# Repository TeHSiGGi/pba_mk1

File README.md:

# PBA MK1

## Introduction

The **P**ortable **B**luetooth **A**mp MK1 is the first iteration of a portable bluetooth amplifier.

The goal was to design a universal base platform for designing bluetooth speaker in a range of small to large power.

The amplifier is meant to be powered by LiPo batteries.

## Repository structure

```text
/pba:mk1
  /docs             # Documentation repository
  /eagle            # Contains eagle files
  /gerber           # Contains gerber board files
  /pdf              # Contains PDF versions of the schematics 
```

## Technical specification

### Power Supply

The power supply provides different voltages for digital and analog purpose.

It provides the following rails:

- `D33` - 3.3V 0.25A Digital - for digital logic and bluetooth module
- `A75` - 7.5V 0.10A Analog - for analog audio processing
- `D120` - 12V 1.00A Digital - Control voltage for Class-D amplifier
- `VAMP` - VBAT - 30V 3.00A - Amplification voltage for Class-D amplifier

The `D33` rail is constantly enabled and provides power for the bluetooth module.

All other rails are enabled on demand by the bluetooth module, via the `EN` signal.

As regulators for all rails expect `VAMP` `LMR50410` are used.

The `VAMP` rail can be varied between `VBAT` and 30V. This is provided by using a `LM5122` boost converter, that will be enabled on demand. If not required, the `LM5122` will go into passthrough mode and disable the boost action. The boost action is controlled via a separate `LVL` signal.

The power supply also provides the capability to charge and use a 4S LiPo battery. Please note: The power supply does **not** provide any balancing or protection circuitry. Those things must be included in your 4S LiPo battery pack.

As charging controller a `LTC4006-6` is used, which incorporates all necessary functionality.
The power supply used to charge the LiPo battery is a 19V external power supply. The input current is limited to 3.07A.

Charging current is limited to 2.00A and the charging timer is configured to approx. 2 hours.

There is currently **no** NTC readout configured in the charging circuit.

As a charger supply, I recommend the use of generic laptop chargers with 19V and 3.54A - they are widely available, reliable and cheap.

### Amplifier and DAC

As amplifiers there are two `TPA3245` used in this project.

The first of them is driven by directly by the `CSR8675` bluetooth chip DAC outputs, using a BTL configuration for two output channels.

The second amplifier is configured in a PBTL configuration and is driven by a `PCM5102` DAC.

The first amplifier should be used for full-range or dedicated mid/migh-range speakers, whereas the second amplifier with its PBTL configuration is meant to drive low-range/subwoofer speakers, since due to its configuration it is able to deliver more current and drive speakers with low impedances.

All analog signals are used differentially to reduce noise and hum. Between the differential DAC output and amplifier inputs there are `TS914` adding amplification to the signals for additional volume.

The amplifiers will automatically be enabled, if music is playing. This is controlled by the `CSR8675` using the `AMP_EN` signal.

There is an additional level detection circuit that will switch the amplifier supply voltage by setting the `LVL` signal to `high`. This allows the amplifier chips to run at a lower voltage for moderate volumes and have enough headroom for high volume music playback. The usage of a higher voltage also allows for better use of higher impedance speakers, such as 8-16Ohms.

The threshold of the level detection can be configured via a potentiometer on the amplifier board.

### Bluetooth

As for bluetooth, the `CSR8675` in form of `BTM-875` modules is used.

That chip provides the following functionality:

- Bluetooth 4.0+ compliance
- Stereo differential analogue audio inputs (used as line-in)
- Stereo differential analogue audio outputs (driving `TPA3245` in BTL configuration)
- I²S output (driving `PCM5102` for second `TPA3245` in PBTL configuration)
- LED and Button GPIOs (3 LEDs and 8 GPIOs are exposed)
- GPIO control for enabling external circuitry (enabling power with `EN` and amplifiers with `AMP_EN`)
- Kalimba DSP (used for crossover and DSP audio processing)
- True Wireless Stereo (can link two amplifiers together playing music in sync)

Software used on the `CSR8675` is configured using the ADK in version 4.1.35.

### Architecture

#### Audio signal paths

#### Power paths

#### GPIO to function mapping

|GPIO|Function|Description|
|--|--|--|
|LED0|User interface LED|Can be used to display status messages.|
|LED1|User interface LED|Can be used to display status messages.|
|LED2|User interface LED|Can be used to display status messages.|
|PIO0|User interface GPIO|Can be used to connect a button for user interaction.|
|PIO1|User interface GPIO|Can be used to connect a button for user interaction.|
|PIO2|User interface GPIO|Can be used to connect a button for user interaction.|
|PIO3|User interface GPIO|Can be used to connect a button for user interaction.|
|PIO4|User interface GPIO|Can be used to connect a button for user interaction.|
|PIO5|User interface GPIO|Can be used to connect a button for user interaction.|
|PIO6|User interface GPIO|Can be used to connect a button for user interaction.|
|PIO7|User interface GPIO|Can be used to connect a button for user interaction.|
|PWR|User interface GPIO|Can be used to connect a button for user interaction.|
|PIO10|DETECT|Used to detect plugged in line-in source.|
|PIO11|AMP_EN|Used to enable amplifiers when music is playing.|
|PIO12|EN|Used to enable the power supply.|
|PIO15|I²S DAC enable|Used to enable the external I²S dac if music is playing.|

### Miscellaneous

Schematics and layouts are created using Eagle.

Gerber files provided have been used to create first batch of boards and working instances of the PBA MK1.

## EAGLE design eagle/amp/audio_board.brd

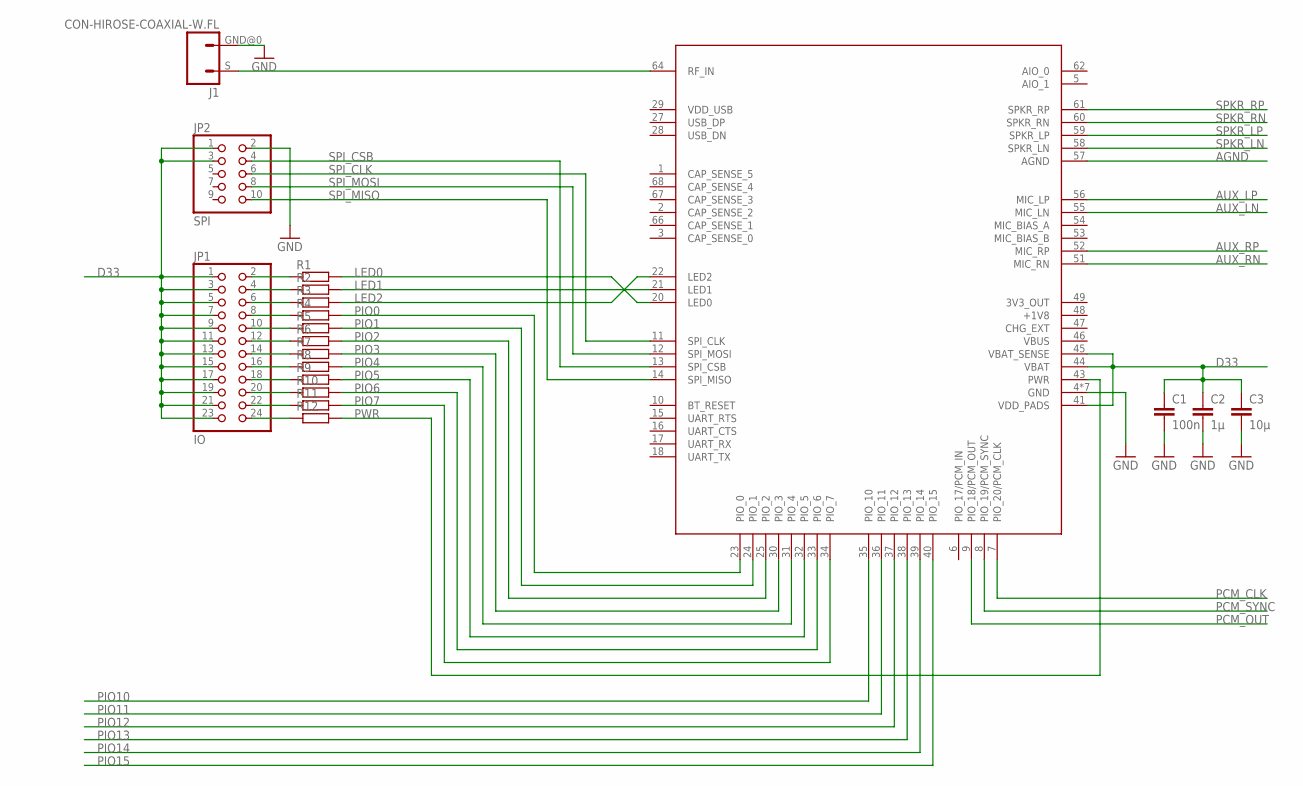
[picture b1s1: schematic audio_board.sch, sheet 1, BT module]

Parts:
BT1: BTM875-B; BTM875
C1: 100n; C0805
C2: 1µ; C0805
C3: 10µ; C0805
J1: CON-HIROSE-COAXIAL-W.FL; CON-W.FL
JP1: IO; 2X12
JP2: SPI; 2X05
R1, R2, R3, R4, R5, R6, R7, R8, R9, R10, R11, R12: R-EU_R0805; R0805

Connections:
AGND: BT1.57 (AGND)
AUX_LN: BT1.55 (MIC_LN); also elsewhere on the board
AUX_LP: BT1.56 (MIC_LP); also elsewhere on the board
AUX_RN: BT1.51 (MIC_RN); also elsewhere on the board
AUX_RP: BT1.52 (MIC_RP); also elsewhere on the board
D33: BT1.41 (VDD_PADS), BT1.44 (VBAT), BT1.45 (VBAT_SENSE), C1.1, C2.1, C3.1, JP1.1, JP1.3, JP1.5, JP1.7, JP1.9, JP1.11, JP1.13, JP1.15, JP1.17, JP1.19, JP1.21, JP1.23, JP2.1, JP2.3; also elsewhere on the board
GND: BT1.4 (GND), BT1.19 (GND), BT1.26 (GND), BT1.42 (GND), BT1.50 (GND), BT1.63 (GND), BT1.65 (GND), C1.2, C2.2, C3.2, J1.GND@0 (2), JP2.2; also elsewhere on the board
LED0: BT1.20 (LED0), R1.2
LED1: BT1.21 (LED1), R2.2
LED2: BT1.22 (LED2), R3.2
unnamed: BT1.64 (RF_IN), J1.S (1)
unnamed: JP1.2, R1.1
unnamed: JP1.4, R2.1
unnamed: JP1.6, R3.1
unnamed: JP1.8, R4.1
unnamed: JP1.10, R5.1
unnamed: JP1.12, R6.1
unnamed: JP1.14, R7.1
unnamed: JP1.16, R8.1
unnamed: JP1.18, R9.1
unnamed: JP1.20, R10.1
unnamed: JP1.22, R11.1
unnamed: JP1.24, R12.1
PCM_CLK: BT1.7 (PIO_20/PCM_CLK); also elsewhere on the board
PCM_OUT: BT1.9 (PIO_18/PCM_OUT); also elsewhere on the board
PCM_SYNC: BT1.8 (PIO_19/PCM_SYNC); also elsewhere on the board
PIO0: BT1.23 (PIO_0), R4.2
PIO1: BT1.24 (PIO_1), R5.2
PIO2: BT1.25 (PIO_2), R6.2
PIO3: BT1.30 (PIO_3), R7.2
PIO4: BT1.31 (PIO_4), R8.2
PIO5: BT1.32 (PIO_5), R9.2
PIO6: BT1.33 (PIO_6), R10.2
PIO7: BT1.34 (PIO_7), R11.2
PIO10: BT1.35 (PIO_10); also elsewhere on the board
PIO11: BT1.36 (PIO_11); also elsewhere on the board
PIO12: BT1.37 (PIO_12); also elsewhere on the board
PIO13: BT1.38 (PIO_13)
PIO14: BT1.39 (PIO_14)
PIO15: BT1.40 (PIO_15); also elsewhere on the board
PWR: BT1.43 (PWR), R12.2
SPI_CLK: BT1.11 (SPI_CLK), JP2.6
SPI_CSB: BT1.13 (SPI_CSB), JP2.4
SPI_MISO: BT1.14 (SPI_MISO), JP2.10
SPI_MOSI: BT1.12 (SPI_MOSI), JP2.8
SPKR_LN: BT1.58 (SPKR_LN); also elsewhere on the board
SPKR_LP: BT1.59 (SPKR_LP); also elsewhere on the board
SPKR_RN: BT1.60 (SPKR_RN); also elsewhere on the board
SPKR_RP: BT1.61 (SPKR_RP); also elsewhere on the board

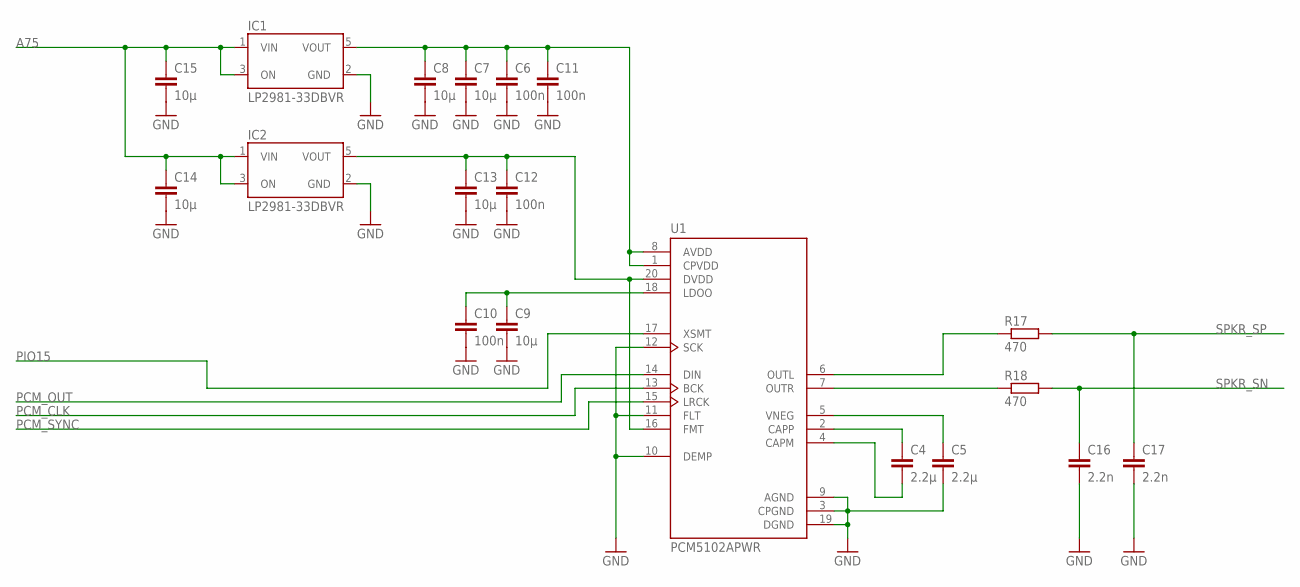
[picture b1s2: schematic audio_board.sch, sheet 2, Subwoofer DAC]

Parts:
C4, C5: 2.2µ; C0805
C6, C10, C11, C12: 100n; C0805
C7, C8, C9, C13, C14, C15: 10µ; C0805
C16, C17: 2.2n; C0805
IC1, IC2: LP2981-33DBVR; SOT23-5
R17, R18: 470; M0805
U1: PCM5102APWR; SOP65P640X120-20N

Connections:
A33DAC: C6.1, C7.1, C8.1, C11.1, IC1.5 (VOUT), U1.1 (CPVDD), U1.8 (AVDD)
A75: C14.1, C15.1, IC1.1 (VIN), IC1.3 (ON), IC2.1 (VIN), IC2.3 (ON); also elsewhere on the board
D33DAC: C12.1, C13.1, IC2.5 (VOUT), U1.16 (FMT), U1.20 (DVDD)
GND: C5.2, C6.2, C7.2, C8.2, C9.2, C10.2, C11.2, C12.2, C13.2, C14.2, C15.2, C16.2, C17.2, IC1.2 (GND), IC2.2 (GND), U1.3 (CPGND), U1.9 (AGND), U1.10 (DEMP), U1.11 (FLT), U1.12 (SCK), U1.19 (DGND); also elsewhere on the board
unnamed: C4.1, U1.2 (CAPP)
unnamed: C4.2, U1.4 (CAPM)
unnamed: C5.1, U1.5 (VNEG)
unnamed: C9.1, C10.1, U1.18 (LDOO)
unnamed: R18.1, U1.7 (OUTR)
unnamed: R17.1, U1.6 (OUTL)
PCM_CLK: U1.13 (BCK); also elsewhere on the board
PCM_OUT: U1.14 (DIN); also elsewhere on the board
PCM_SYNC: U1.15 (LRCK); also elsewhere on the board
PIO15: U1.17 (XSMT); also elsewhere on the board
SPKR_SN: C16.1, R18.2; also elsewhere on the board
SPKR_SP: C17.1, R17.2; also elsewhere on the board

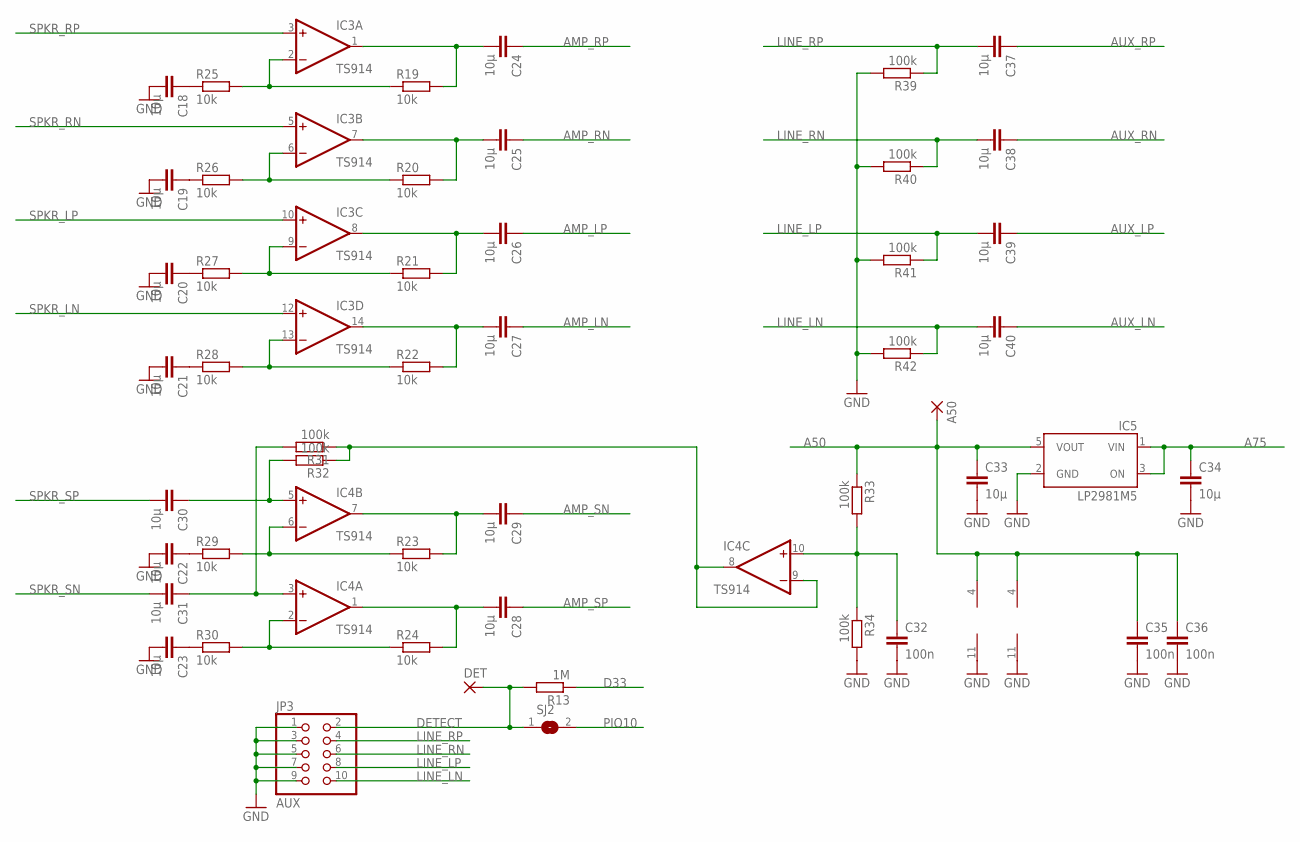
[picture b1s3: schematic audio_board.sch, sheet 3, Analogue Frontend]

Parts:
A50: SMD2; SMD1,27-2,54
C18, C19, C20, C21, C22, C23, C24, C25, C26, C27, C28, C29, C30, C31, C33, C34, C37, C38, C39, C40: 10µ; C0805
C32, C35, C36: 100n; C0805
DET: SMD2; SMD1,27-2,54
IC3, IC4: TS914; SO14
IC5: LP2981M5; SOT23-5
JP3: AUX; 2X05
R13: 1M; R0805
R19, R20, R21, R22, R23, R24, R25, R26, R27, R28, R29, R30: 10k; R0805
R31, R32, R33, R34, R39, R40, R41, R42: 100k; R0805
SJ2: SJ

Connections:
A25BIAS: IC4.8 (OUT), IC4.9 (-IN), R31.1, R32.1
A50: A50.1, C33.1, C35.1, C36.1, IC3.4 (V+), IC4.4 (V+), IC5.5 (VOUT), R33.1; also elsewhere on the board
A75: C34.1, IC5.1 (VIN), IC5.3 (ON); also elsewhere on the board
AMP_LN: C27.1; also elsewhere on the board
AMP_LP: C26.1; also elsewhere on the board
AMP_RN: C25.1; also elsewhere on the board
AMP_RP: C24.1; also elsewhere on the board
AMP_SN: C29.1; also elsewhere on the board
AMP_SP: C28.1; also elsewhere on the board
AUX_LN: C40.1; also elsewhere on the board
AUX_LP: C39.1; also elsewhere on the board
AUX_RN: C38.1; also elsewhere on the board
AUX_RP: C37.1; also elsewhere on the board
D33: R13.1; also elsewhere on the board
DETECT: DET.1, JP3.2, R13.2, SJ2.1
GND: C18.2, C19.2, C20.2, C21.2, C22.2, C23.2, C32.2, C33.2, C34.2, C35.2, C36.2, IC3.11 (V-), IC4.11 (V-), IC5.2 (GND), JP3.1, JP3.3, JP3.5, JP3.7, JP3.9, R34.2, R39.2, R40.2, R41.2, R42.2; also elsewhere on the board
LINE_LN: C40.2, JP3.10, R42.1
LINE_LP: C39.2, JP3.8, R41.1
LINE_RN: C38.2, JP3.6, R40.1
LINE_RP: C37.2, JP3.4, R39.1
unnamed: C18.1, R25.1
unnamed: C19.1, R26.1
unnamed: C20.1, R27.1
unnamed: C21.1, R28.1
unnamed: C22.1, R29.1
unnamed: C23.1, R30.1
unnamed: IC4.2 (-IN), R24.1, R30.2
unnamed: IC4.6 (-IN), R23.1, R29.2
unnamed: IC3.13 (-IN), R22.1, R28.2
unnamed: IC3.9 (-IN), R21.1, R27.2
unnamed: IC3.6 (-IN), R20.1, R26.2
unnamed: IC3.2 (-IN), R19.1, R25.2
unnamed: C24.2, IC3.1 (OUT), R19.2
unnamed: C25.2, IC3.7 (OUT), R20.2
unnamed: C26.2, IC3.8 (OUT), R21.2
unnamed: C27.2, IC3.14 (OUT), R22.2
unnamed: C29.2, IC4.7 (OUT), R23.2
unnamed: C28.2, IC4.1 (OUT), R24.2
unnamed: C32.1, IC4.10 (+IN), R33.2, R34.1
unnamed: C31.1, IC4.3 (+IN), R31.2
unnamed: C30.1, IC4.5 (+IN), R32.2
PIO10: SJ2.2; also elsewhere on the board
SPKR_LN: IC3.12 (+IN); also elsewhere on the board
SPKR_LP: IC3.10 (+IN); also elsewhere on the board
SPKR_RN: IC3.5 (+IN); also elsewhere on the board
SPKR_RP: IC3.3 (+IN); also elsewhere on the board
SPKR_SN: C31.2; also elsewhere on the board
SPKR_SP: C30.2; also elsewhere on the board

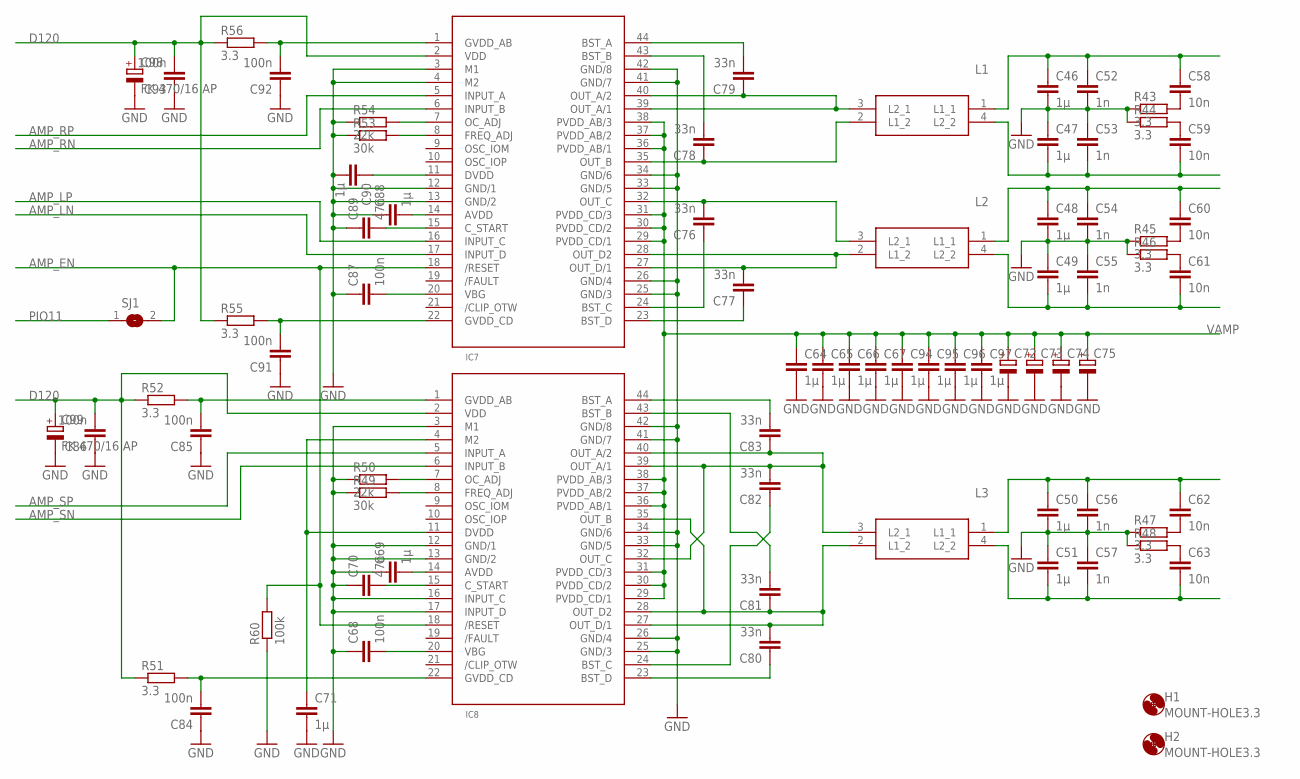
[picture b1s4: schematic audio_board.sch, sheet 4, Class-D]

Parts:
C46, C47, C48, C49, C50, C51: 1µ; C050-075X075
C52, C53, C54, C55, C56, C57: 1n; C0805
C58, C59, C60, C61, C62, C63: 10n; C0805
C64, C65, C66, C67, C69, C71, C88, C90, C94, C95, C96, C97: 1µ; C0805
C68, C84, C85, C86, C87, C91, C92, C93: 100n; C0805
C70, C89: 47n; C0805
C72, C73, C74, C75: CPOL-EU153CLV-0810; 153CLV-0810
C76, C77, C78, C79, C80, C81, C82, C83: 33n; C0805
C98, C99: FK 470/16 AP; 153CLV-0810
H1, H2: MOUNT-HOLE3.3; 3,3
IC7, IC8: TPA3255; POWERPAD-TSSOP-44
L1, L2, L3: UA8014-ALD; UA8014ALD
R43, R44, R45, R46, R47, R48, R51, R52, R55, R56: 3.3; R0805
R49, R53: 30k; R0805
R50, R54: 22k; R0805
R60: 100k; R0805
SJ1: SJ

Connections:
AMP_EN: IC7.18 (/RESET), IC8.18 (/RESET), R60.2, SJ1.2
AMP_LN: IC7.17 (INPUT_D); also elsewhere on the board
AMP_LP: IC7.16 (INPUT_C); also elsewhere on the board
AMP_RN: IC7.6 (INPUT_B); also elsewhere on the board
AMP_RP: IC7.5 (INPUT_A); also elsewhere on the board
AMP_SN: IC8.6 (INPUT_B); also elsewhere on the board
AMP_SP: IC8.5 (INPUT_A); also elsewhere on the board
D120: C86.2, C93.2, C98.+, C99.+, IC7.2 (VDD), IC8.2 (VDD), R51.1, R52.1, R55.1, R56.1; also elsewhere on the board
GND: C46.2, C47.1, C48.2, C49.1, C50.2, C51.1, C52.2, C53.1, C54.2, C55.1, C56.2, C57.1, C64.2, C65.2, C66.2, C67.2, C68.1, C69.1, C70.1, C71.2, C72.-, C73.-, C74.-, C75.-, C84.1, C85.1, C86.1, C87.1, C88.1, C89.1, C90.2, C91.1, C92.1, C93.1, C94.2, C95.2, C96.2, C97.2, C98.-, C99.-, IC7.3 (M1), IC7.4 (M2), IC7.12 (GND/1), IC7.13 (GND/2), IC7.25 (GND/3), IC7.26 (GND/4), IC7.33 (GND/5), IC7.34 (GND/6), IC7.41 (GND/7), IC7.42 (GND/8), IC8.3 (M1), IC8.12 (GND/1), IC8.13 (GND/2), IC8.16 (INPUT_C), IC8.17 (INPUT_D), IC8.25 (GND/3), IC8.26 (GND/4), IC8.33 (GND/5), IC8.34 (GND/6), IC8.41 (GND/7), IC8.42 (GND/8), R43.1, R44.1, R45.1, R46.1, R47.1, R48.1, R49.1, R50.1, R53.1, R54.1, R60.1; also elsewhere on the board
LN: C49.2, C55.2, C61.2, L2.4 (L2_2); also elsewhere on the board
LP: C48.1, C54.1, C60.1, L2.1 (L1_1); also elsewhere on the board
unnamed: C79.1, IC7.39 (OUT_A/1), IC7.40 (OUT_A/2), L1.3 (L2_1)
unnamed: C78.1, IC7.35 (OUT_B), L1.2 (L1_2)
unnamed: C77.2, IC7.27 (OUT_D/1), IC7.28 (OUT_D2), L2.2 (L1_2)
unnamed: C76.2, IC7.32 (OUT_C), L2.3 (L2_1)
unnamed: C58.2, R43.2
unnamed: C59.1, R44.2
unnamed: C60.2, R45.2
unnamed: C61.1, R46.2
unnamed: C62.2, R47.2
unnamed: C63.1, R48.2
unnamed: C79.2, IC7.44 (BST_A)
unnamed: C78.2, IC7.43 (BST_B)
unnamed: C76.1, IC7.24 (BST_C)
unnamed: C71.1, IC8.4 (M2), IC8.11 (DVDD)
unnamed: IC8.7 (OC_ADJ), R50.2
unnamed: C77.1, IC7.23 (BST_D)
unnamed: C82.2, C83.1, IC8.32 (OUT_C), IC8.39 (OUT_A/1), IC8.40 (OUT_A/2), L3.3 (L2_1)
unnamed: C80.2, C81.1, IC8.27 (OUT_D/1), IC8.28 (OUT_D2), IC8.35 (OUT_B), L3.2 (L1_2)
unnamed: C83.2, IC8.44 (BST_A)
unnamed: C80.1, IC8.23 (BST_D)
unnamed: C82.1, IC8.24 (BST_C)
unnamed: C81.2, IC8.43 (BST_B)
unnamed: C68.2, IC8.20 (VBG)
unnamed: C69.2, IC8.14 (AVDD)
unnamed: C70.2, IC8.15 (C_START)
unnamed: IC8.8 (FREQ_ADJ), R49.2
unnamed: C85.2, IC8.1 (GVDD_AB), R52.2
unnamed: C84.2, IC8.22 (GVDD_CD), R51.2
unnamed: C90.1, IC7.11 (DVDD)
unnamed: C87.2, IC7.20 (VBG)
unnamed: C88.2, IC7.14 (AVDD)
unnamed: C89.2, IC7.15 (C_START)
unnamed: IC7.7 (OC_ADJ), R54.2
unnamed: IC7.8 (FREQ_ADJ), R53.2
unnamed: C92.2, IC7.1 (GVDD_AB), R56.2
unnamed: C91.2, IC7.22 (GVDD_CD), R55.2
PIO11: SJ1.1; also elsewhere on the board
RN: C47.2, C53.2, C59.2, L1.4 (L2_2); also elsewhere on the board
RP: C46.1, C52.1, C58.1, L1.1 (L1_1); also elsewhere on the board
SUBN: C51.2, C57.2, C63.2, L3.4 (L2_2); also elsewhere on the board
SUBP: C50.1, C56.1, C62.1, L3.1 (L1_1); also elsewhere on the board
VAMP: C64.1, C65.1, C66.1, C67.1, C72.+, C73.+, C74.+, C75.+, C94.1, C95.1, C96.1, C97.1, IC7.29 (PVDD_CD/1), IC7.30 (PVDD_CD/2), IC7.31 (PVDD_CD/3), IC7.36 (PVDD_AB/1), IC7.37 (PVDD_AB/2), IC7.38 (PVDD_AB/3), IC8.29 (PVDD_CD/1), IC8.30 (PVDD_CD/2), IC8.31 (PVDD_CD/3), IC8.36 (PVDD_AB/1), IC8.37 (PVDD_AB/2), IC8.38 (PVDD_AB/3); also elsewhere on the board

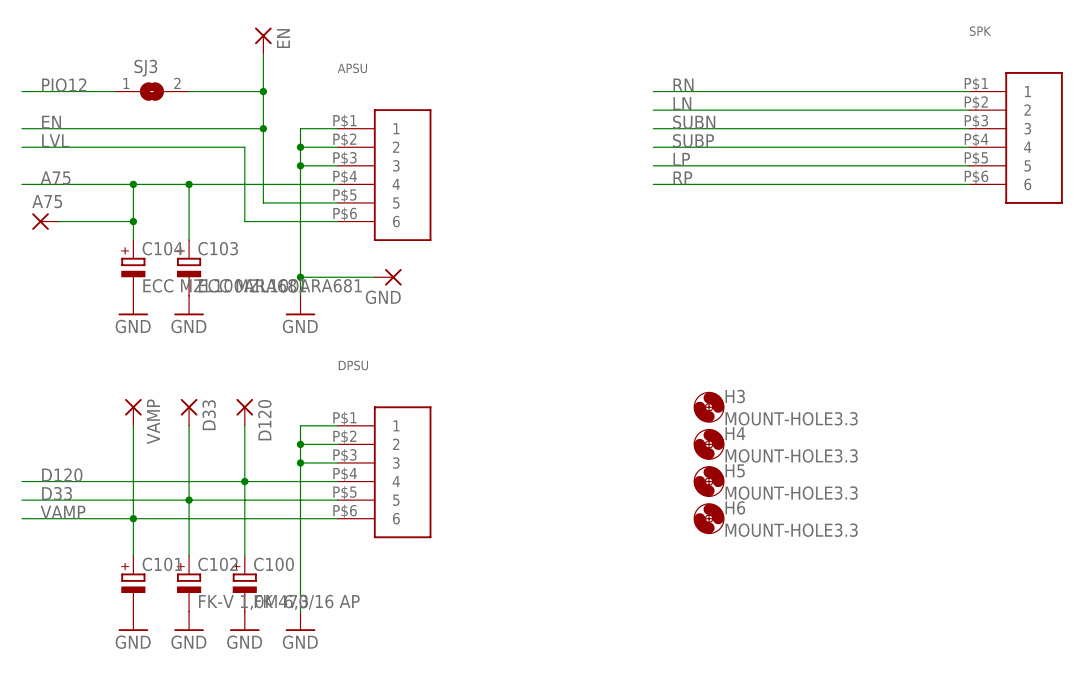
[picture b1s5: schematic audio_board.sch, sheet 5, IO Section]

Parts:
A75: SMD2; SMD1,27-2,54
APSU: 39-30-1060_BLANK; 5569_6P
C100: FK 470/16 AP; 153CLV-0810
C101: CPOL-EU153CLV-0810; 153CLV-0810
C102: FK-V 1,0M 6,3; 153CLV-0810
C103, C104: ECC MZL100ARA681; 153CLV-0810
D33, D120: SMD2; SMD1,27-2,54
DPSU: 39-30-1060_BLANK; 5569_6P
EN: SMD2; SMD1,27-2,54
GND: SMD2; SMD1,27-2,54
H3, H4, H5, H6: MOUNT-HOLE3.3; 3,3
SJ3: SJ
SPK: 39-30-1060_BLANK; 5569_6P
VAMP: SMD2; SMD1,27-2,54

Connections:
A75: A75.1, APSU.P$4 (4), C103.+, C104.+; also elsewhere on the board
D33: C102.+, D33.1, DPSU.P$5 (5); also elsewhere on the board
D120: C100.+, D120.1, DPSU.P$4 (4); also elsewhere on the board
EN: APSU.P$5 (5), EN.1, SJ3.2
GND: APSU.P$1 (1), APSU.P$2 (2), APSU.P$3 (3), C100.-, C101.-, C102.-, C103.-, C104.-, DPSU.P$1 (1), DPSU.P$2 (2), DPSU.P$3 (3), GND.1; also elsewhere on the board
LN: SPK.P$2 (2); also elsewhere on the board
LP: SPK.P$5 (5); also elsewhere on the board
LVL: APSU.P$6 (6); also elsewhere on the board
PIO12: SJ3.1; also elsewhere on the board
RN: SPK.P$1 (1); also elsewhere on the board
RP: SPK.P$6 (6); also elsewhere on the board
SUBN: SPK.P$3 (3); also elsewhere on the board
SUBP: SPK.P$4 (4); also elsewhere on the board
VAMP: C101.+, DPSU.P$6 (6), VAMP.1; also elsewhere on the board

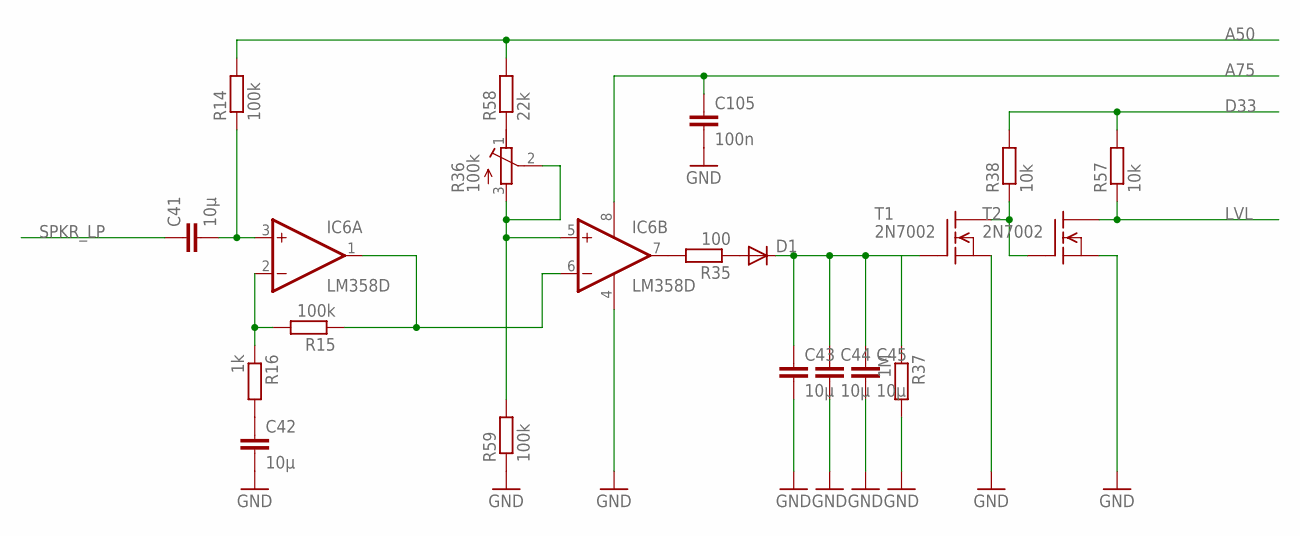
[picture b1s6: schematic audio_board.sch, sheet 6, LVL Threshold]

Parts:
C41, C42, C43, C44, C45: 10µ; C0805
C105: 100n; C0805
D1: DIODE-DO214AC; DO214AC
IC6: LM358D; SO08
R14, R15, R59: 100k; M0805
R16: 1k; M0805
R35: 100; M0805
R36: 100k; RTRIM3314G
R37: 1M; M0805
R38, R57: 10k; M0805
R58: 22k; M0805
T1, T2: 2N7002; SOT23

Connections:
A50: R14.2, R58.2; also elsewhere on the board
A75: C105.1, IC6.8 (V+); also elsewhere on the board
D33: R38.2, R57.2; also elsewhere on the board
GND: C42.2, C43.2, C44.2, C45.2, C105.2, IC6.4 (V-), R37.2, R59.1, T1.2 (S), T2.2 (S); also elsewhere on the board
LVL: R57.1, T2.3 (D); also elsewhere on the board
unnamed: C41.2, IC6.3 (+IN), R14.1
unnamed: C42.1, R16.2
unnamed: IC6.2 (-IN), R15.2, R16.1
unnamed: IC6.1 (OUT), IC6.6 (-IN), R15.1
unnamed: R38.1, T1.3 (D), T2.1 (G)
unnamed: R36.1 (E), R58.1
unnamed: IC6.7 (OUT), R35.2
unnamed: D1.A, R35.1
unnamed: C43.1, C44.1, C45.1, D1.C, R37.1, T1.1 (G)
unnamed: IC6.5 (+IN), R36.2 (S), R36.3 (A), R59.2
SPKR_LP: C41.1; also elsewhere on the board

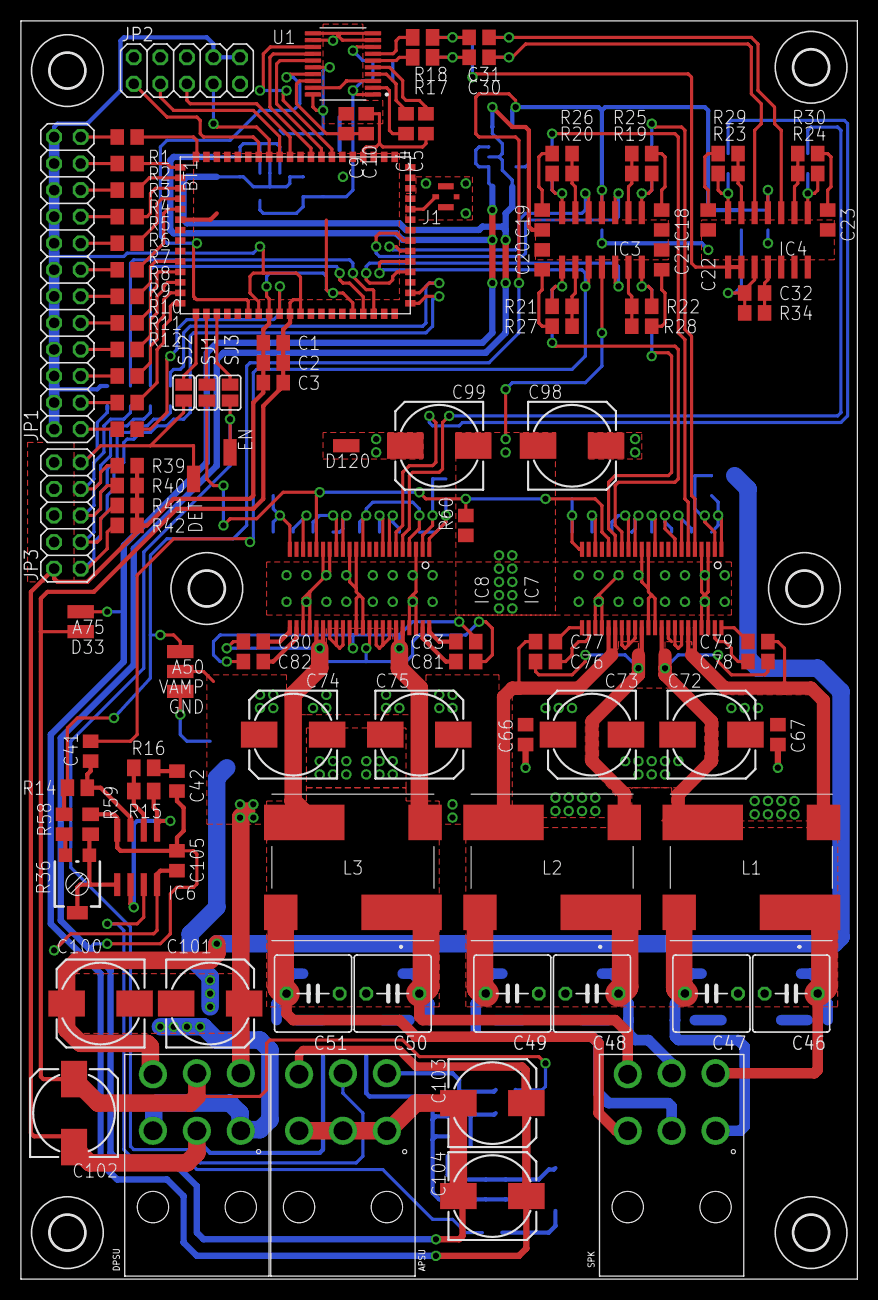
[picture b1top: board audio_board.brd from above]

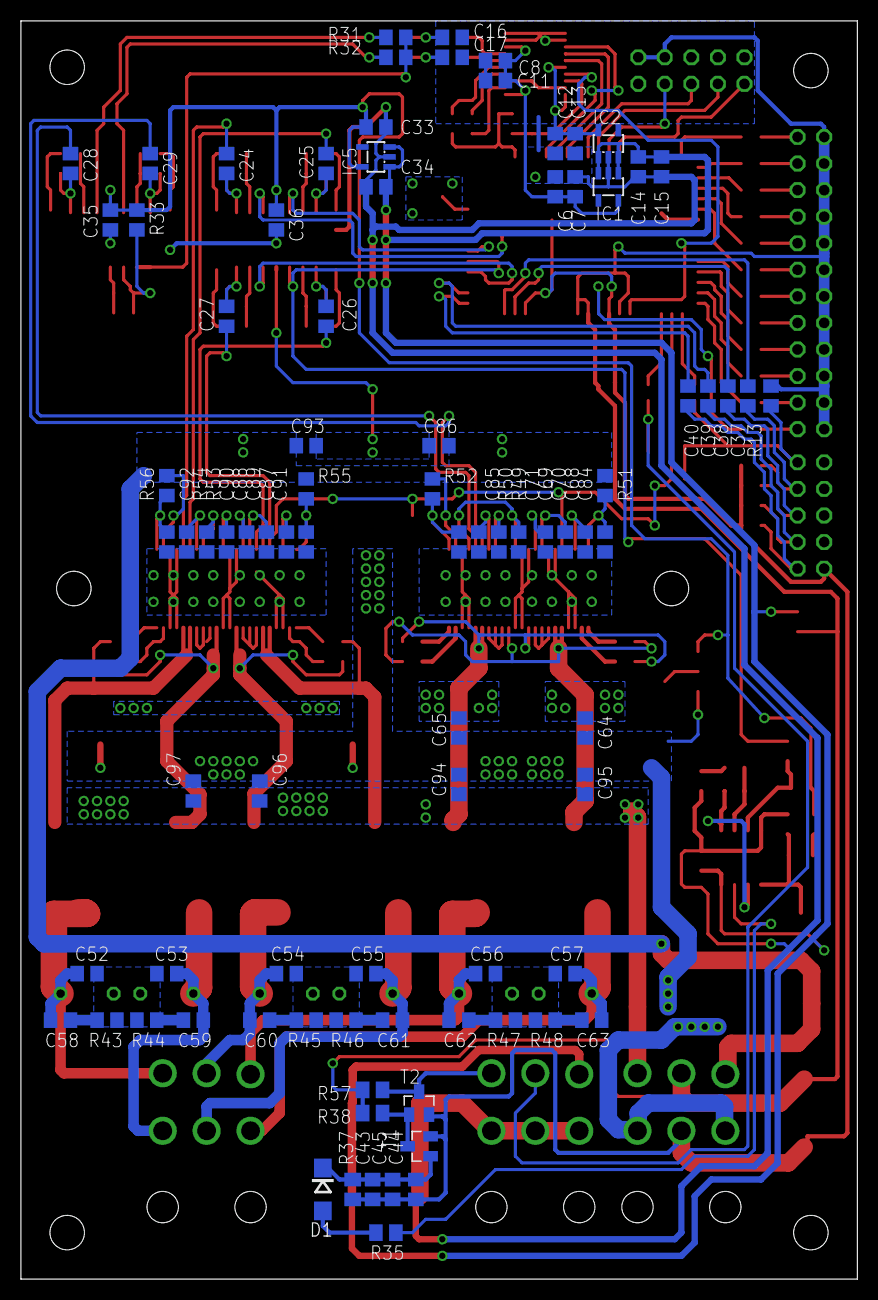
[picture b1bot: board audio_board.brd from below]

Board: 2 copper layers, 80.0 x 120.3 mm, 205 parts (87 on the bottom side), 148 nets.

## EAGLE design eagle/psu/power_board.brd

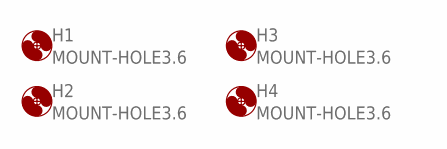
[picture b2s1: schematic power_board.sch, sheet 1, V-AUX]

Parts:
H1, H2, H3, H4: MOUNT-HOLE3.6; 3,6

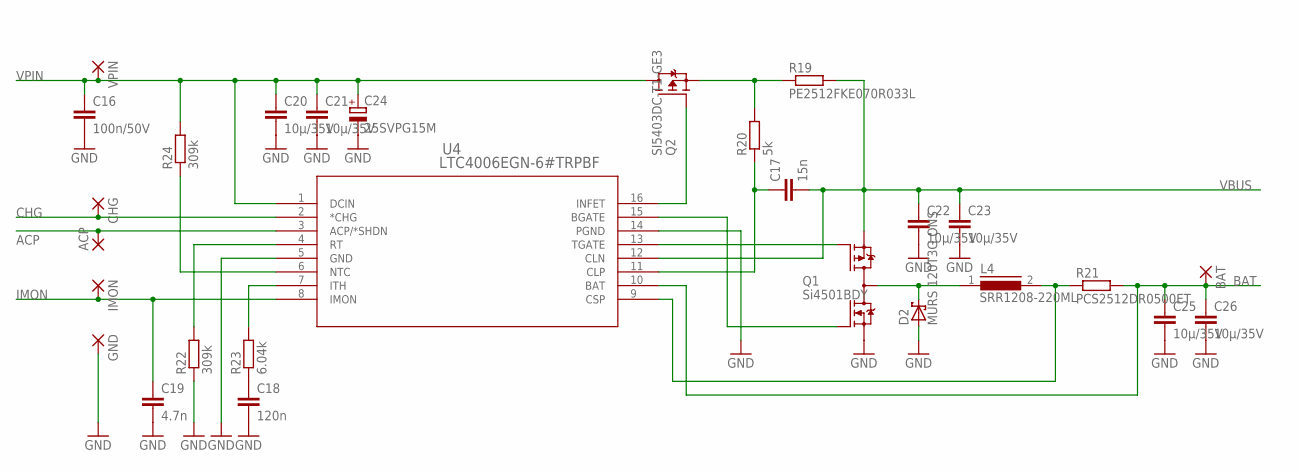
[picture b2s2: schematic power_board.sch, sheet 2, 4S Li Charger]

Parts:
ACP: SMD2; SMD1,27-2,54
BAT: SMD2; SMD1,27-2,54
C16: 100n/50V; C1206
C17: 15n; C0805
C18: 120n; C0805
C19: 4.7n; C0805
C20, C21, C22, C23, C25, C26: 10µ/35V; C1206
C24: 25SVPG15M; 153CLV-0505
CHG: SMD2; SMD1,27-2,54
D2: MURS 120T3G ONS; SMB
GND: SMD2; SMD1,27-2,54
IMON: SMD2; SMD1,27-2,54
L4: SRR1208-220ML; DR127
Q1: Si4501BDY; SO08-IRF
Q2: SI5403DC-T1-GE3; 1206-8CHIP-FET
R19: PE2512FKE070R033L; R2512
R20: 5k; R0805
R21: PCS2512DR0500ET; R2512
R22, R24: 309k; R0805
R23: 6.04k; R0805
U4: LTC4006EGN-6#TRPBF; SSOP-16_GN
VPIN: SMD2; SMD1,27-2,54

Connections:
ACP: ACP.1, U4.3 (ACP/*SHDN)
BAT: BAT.1, C25.1, C26.1, R21.2, U4.10 (BAT); also elsewhere on the board
CHG: CHG.1, U4.2 (*CHG)
GND: C16.2, C18.2, C19.2, C20.2, C21.2, C22.2, C23.2, C24.-, C25.2, C26.2, D2.A, GND.1, Q1.1 (N-S), R22.1, U4.5 (GND), U4.14 (PGND); also elsewhere on the board
IMON: C19.1, IMON.1, U4.8 (IMON)
unnamed: Q2.4 (G), U4.16 (INFET)
unnamed: Q2.5 (S), R19.1, R20.2
unnamed: Q1.4 (P-G), U4.13 (TGATE)
unnamed: Q1.2 (N-G), U4.15 (BGATE)
unnamed: C17.1, R20.1, U4.11 (CLP)
unnamed: C18.1, R23.1
unnamed: D2.C, L4.1, Q1.5 (D), Q1.6 (D), Q1.7 (D), Q1.8 (D)
unnamed: L4.2, R21.1, U4.9 (CSP)
unnamed: R22.2, U4.4 (RT)
unnamed: R23.2, U4.7 (ITH)
unnamed: R24.1, U4.6 (NTC)
VBUS: C17.2, C22.1, C23.1, Q1.3 (P-S), R19.2, U4.12 (CLN); also elsewhere on the board
VPIN: C16.1, C20.1, C21.1, C24.+, Q2.1 (D), Q2.2 (D), Q2.3 (D), Q2.6 (D), Q2.7 (D), Q2.8 (D), R24.2, U4.1 (DCIN), VPIN.1; also elsewhere on the board

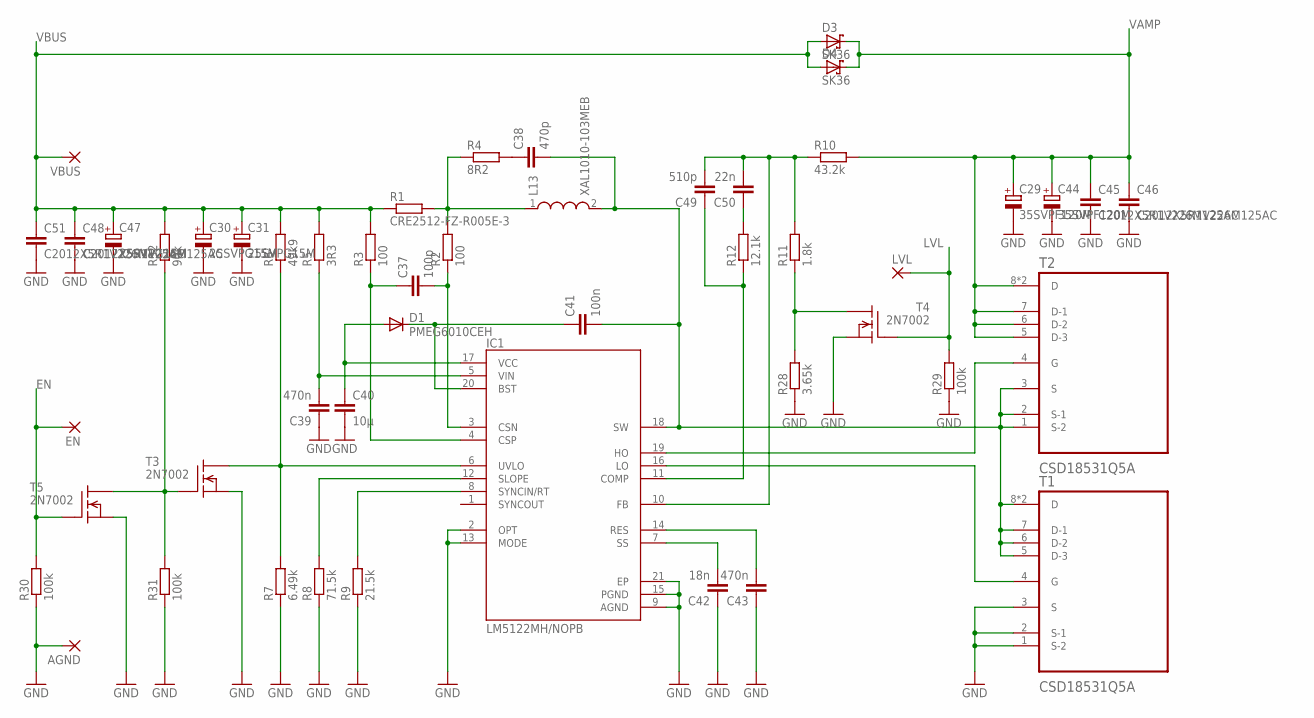
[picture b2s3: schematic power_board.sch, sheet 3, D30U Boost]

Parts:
AGND: SMD2; SMD1,27-2,54
C29, C44: 35SVPF120M; 153CLV-1012
C30, C31, C47: 25SVPG15M; 153CLV-0505
C37: 100p; C0805
C38: 470p; C0805
C39, C43: 470n; C0805
C40: 10µ; C1206
C41: 100n; C0805
C42: 18n; C0805
C45, C46, C48, C51: C2012X5R1V226M125AC; C0805
C49: 510p; C0805
C50: 22n; C0805
D1: PMEG6010CEH; SOD323-W
D3, D4: SK36; SMB
EN: SMD2; SMD1,27-2,54
IC1: LM5122MH/NOPB; SOP65P640X110-21N
L13: XAL1010-103MEB; INDC110100X1000N
LVL: SMD2; SMD1,27-2,54
R1: CRE2512-FZ-R005E-3; R2512
R2, R3: 100; R0805
R4: 8R2; M0805
R5: 3R3; R0805
R6: 49k9; R0805
R7: 6.49k; R0805
R8: 71.5k; R0805
R9: 21.5k; R0805
R10: 43.2k; R0805
R11: 1.8k; R0805
R12: 12.1k; R0805
R28: 3.65k; R0805
R29, R30, R31: 100k; R0805
R32: 90k; R0805
T1, T2: CSD18531Q5A; MOSFET_CSD19531Q5A
T3, T4, T5: 2N7002; SOT23
VBUS: SMD2; SMD1,27-2,54

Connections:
EN: EN.1, R30.2, T5.1 (G); also elsewhere on the board
GND: AGND.1, C29.-, C30.-, C31.-, C39.1, C40.2, C42.1, C43.1, C44.-, C45.2, C46.2, C47.-, C48.2, C51.2, IC1.2 (OPT), IC1.9 (AGND), IC1.13 (MODE), IC1.15 (PGND), IC1.21 (EP), R7.1, R8.1, R9.1, R28.1, R29.1, R30.1, R31.1, T1.1 (S-2), T1.2 (S-1), T1.3 (S), T3.2 (S), T4.2 (S), T5.2 (S); also elsewhere on the board
LVL: LVL.1, R29.2, T4.1 (G); also elsewhere on the board
unnamed: R11.1, R28.2, T4.3 (D)
unnamed: R31.2, R32.1, T3.1 (G), T5.3 (D)
unnamed: C38.2, C41.2, IC1.18 (SW), L13.2, T1.5 (D-3), T1.6 (D-2), T1.7 (D-1), T1.8 (D), T1.9 (D), T2.1 (S-2), T2.2 (S-1), T2.3 (S)
unnamed: C41.1, D1.C, IC1.20 (BST)
unnamed: L13.1, R1.2, R2.2, R4.1
unnamed: C38.1, R4.2
unnamed: C37.2, IC1.3 (CSN), R2.1
unnamed: C37.1, IC1.4 (CSP), R3.1
unnamed: IC1.19 (HO), T2.4 (G)
unnamed: IC1.16 (LO), T1.4 (G)
unnamed: C39.2, IC1.5 (VIN), R5.1
unnamed: C40.1, D1.A, IC1.17 (VCC)
unnamed: IC1.6 (UVLO), R6.1, R7.2, T3.3 (D)
unnamed: IC1.12 (SLOPE), R8.2
unnamed: IC1.8 (SYNCIN/RT), R9.2
unnamed: C42.2, IC1.7 (SS)
unnamed: C43.2, IC1.14 (RES)
unnamed: C49.2, C50.2, IC1.10 (FB), R10.1, R11.2
unnamed: C50.1, R12.2
unnamed: C49.1, IC1.11 (COMP), R12.1
VAMP: C29.+, C44.+, C45.1, C46.1, D3.C, D4.C, R10.2, T2.5 (D-3), T2.6 (D-2), T2.7 (D-1), T2.8 (D), T2.9 (D); also elsewhere on the board
VBUS: C30.+, C31.+, C47.+, C48.1, C51.1, D3.A, D4.A, R1.1, R3.2, R5.2, R6.2, R32.2, VBUS.1; also elsewhere on the board

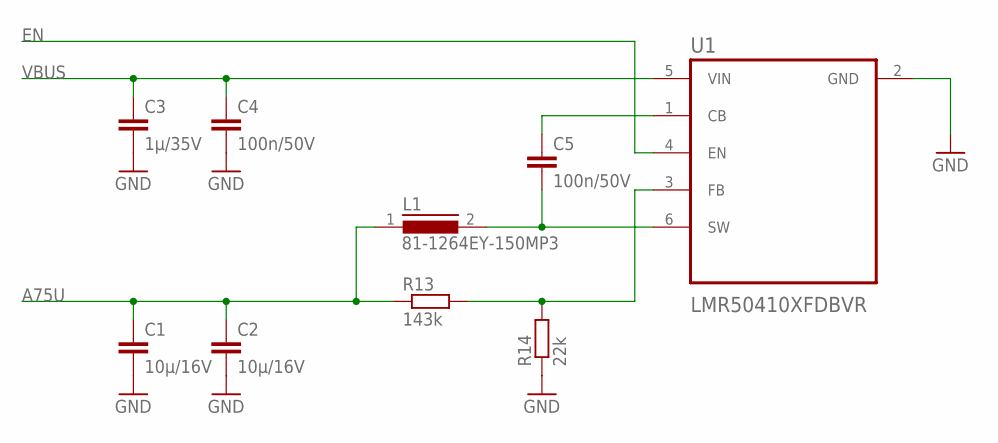
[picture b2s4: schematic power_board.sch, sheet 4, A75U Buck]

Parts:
C1, C2: 10µ/16V; C1206
C3: 1µ/35V; C1206
C4, C5: 100n/50V; C1206
L1: 81-1264EY-150MP3; DR73
R13: 143k; M0805
R14: 22k; M0805
U1: LMR50410XFDBVR; SOT95P280X145-6N

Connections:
A75U: C1.1, C2.1, L1.1, R13.1; also elsewhere on the board
EN: U1.4 (EN); also elsewhere on the board
GND: C1.2, C2.2, C3.2, C4.2, R14.1, U1.2 (GND); also elsewhere on the board
unnamed: C5.1, U1.1 (CB)
unnamed: C5.2, L1.2, U1.6 (SW)
unnamed: R13.2, R14.2, U1.3 (FB)
VBUS: C3.1, C4.1, U1.5 (VIN); also elsewhere on the board

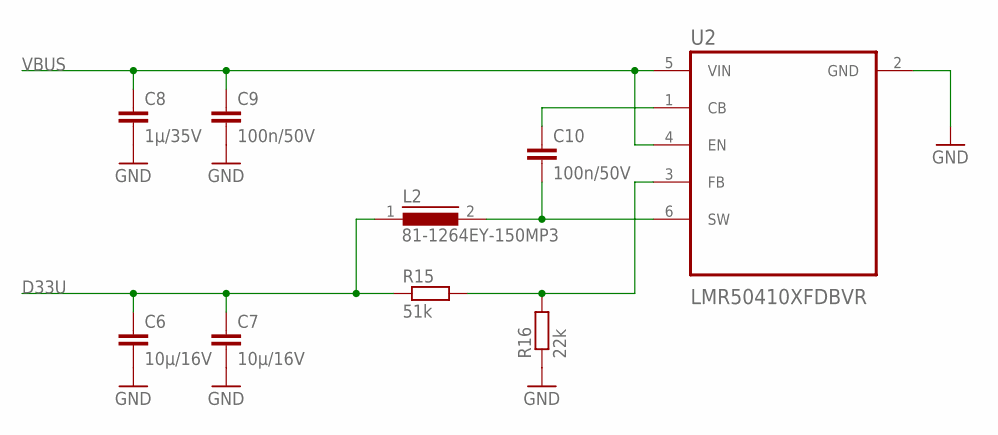
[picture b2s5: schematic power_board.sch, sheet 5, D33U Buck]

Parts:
C6, C7: 10µ/16V; C1206
C8: 1µ/35V; C1206
C9, C10: 100n/50V; C1206
L2: 81-1264EY-150MP3; DR73
R15: 51k; M0805
R16: 22k; M0805
U2: LMR50410XFDBVR; SOT95P280X145-6N

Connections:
D33U: C6.1, C7.1, L2.1, R15.1; also elsewhere on the board
GND: C6.2, C7.2, C8.2, C9.2, R16.1, U2.2 (GND); also elsewhere on the board
unnamed: C10.1, U2.1 (CB)
unnamed: C10.2, L2.2, U2.6 (SW)
unnamed: R15.2, R16.2, U2.3 (FB)
VBUS: C8.1, C9.1, U2.4 (EN), U2.5 (VIN); also elsewhere on the board

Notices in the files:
parts and their libraries:
m-pad-2.1: License : GNU General Public License version 2 (see bottom)
